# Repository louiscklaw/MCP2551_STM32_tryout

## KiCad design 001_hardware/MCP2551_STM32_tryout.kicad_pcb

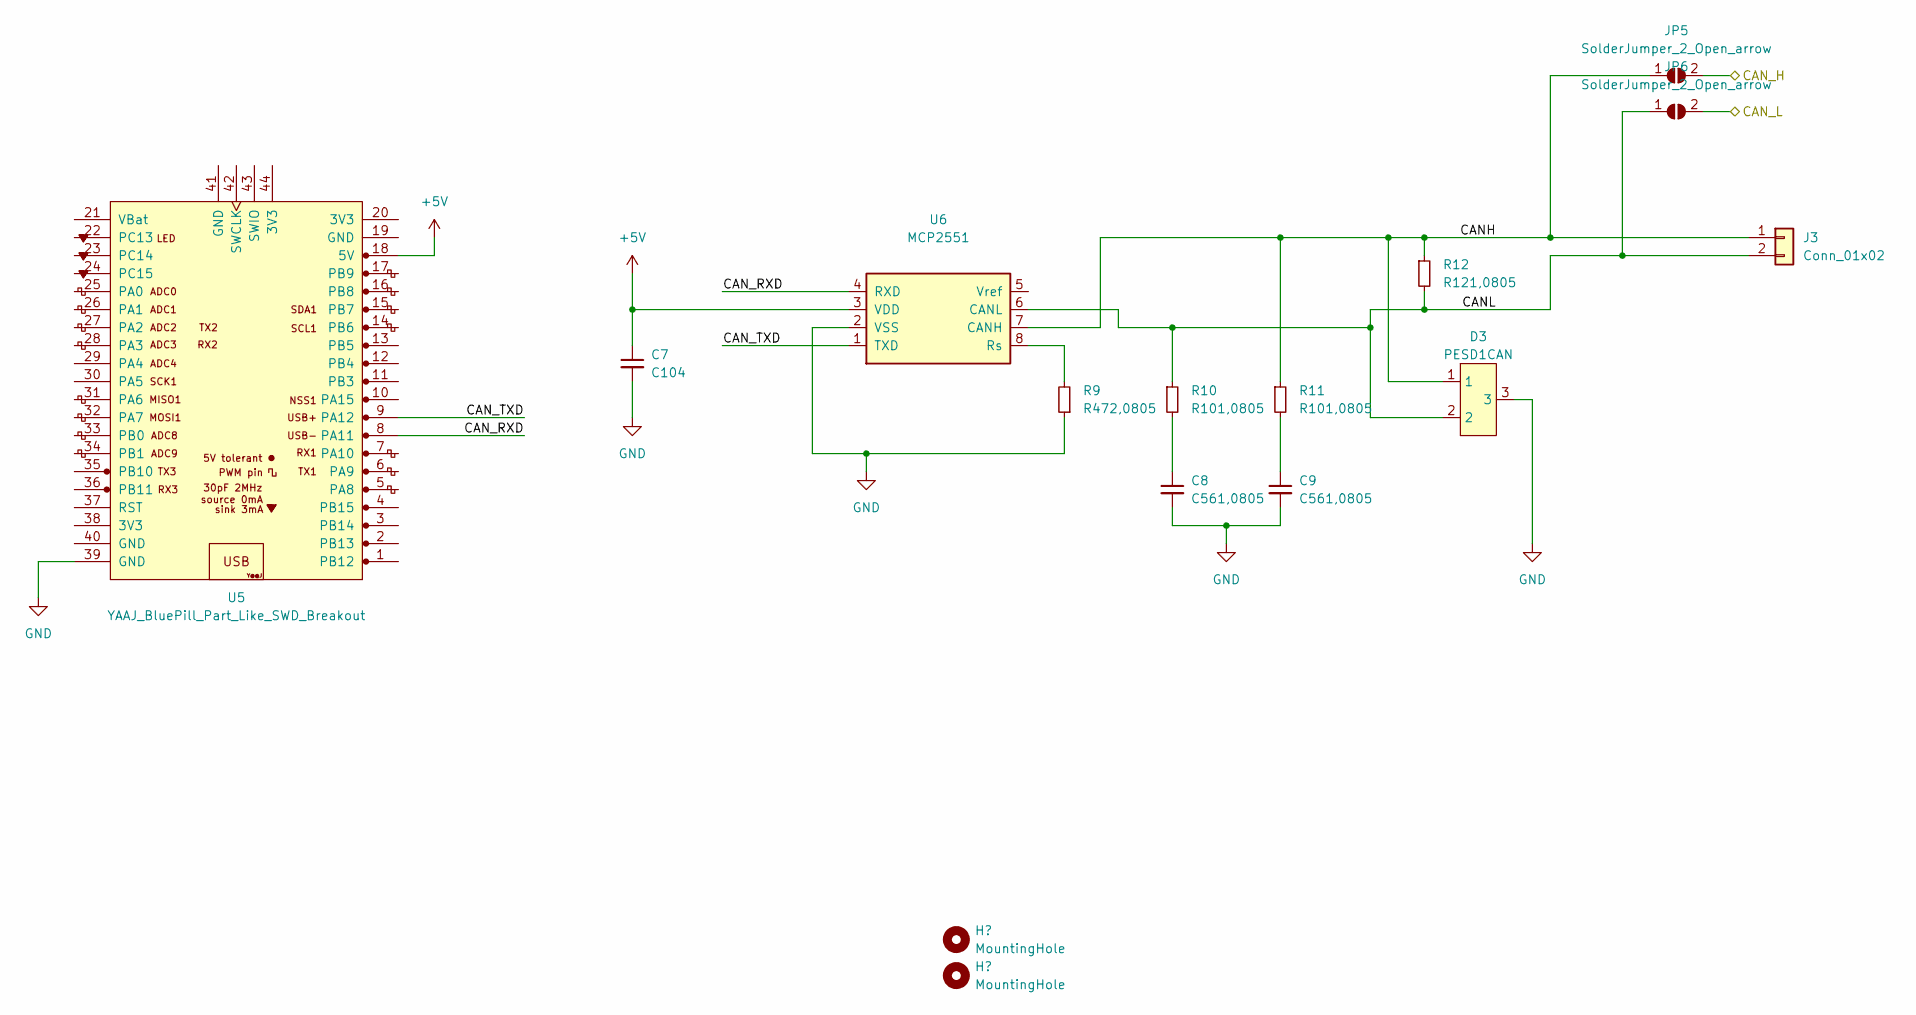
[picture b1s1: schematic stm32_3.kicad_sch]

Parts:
C7: C104; C_0805_2012Metric
C8, C9: C561,0805; C_0805_2012Metric
D3: PESD1CAN; SOT-23
J3: Conn_01x02; PinSocket_1x02_P2.54mm_Vertical
JP5, JP6: SolderJumper_2_Open_arrow; SolderJumper-2_P1.3mm_Open_TrianglePad1.0x1.5mm
R9: R472,0805; R_0805_2012Metric
R10, R11: R101,0805; R_0805_2012Metric
R12: R121,0805; R_0805_2012Metric
U5: YAAJ_BluePill_Part_Like_SWD_Breakout; YAAJ_BluePill_SWD_2
U6: MCP2551; SOIC-8_3.9x4.9mm_P1.27mm

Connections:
+5V: C7.1, U5.18 (5V), U6.3 (VDD); also elsewhere on the board
/stm32_1/CAN_H: JP5.2 (B); also elsewhere on the board
/stm32_1/CAN_L: JP6.2 (B); also elsewhere on the board
/stm32_3/CANH: D3.1, J3.1, JP5.1 (A), R11.1, R12.1, U6.7 (CANH)
/stm32_3/CANL: D3.2, J3.2, JP6.1 (A), R10.1, R12.2, U6.6 (CANL)
/stm32_3/CAN_RXD: U5.8 (PA11), U6.4 (RXD)
/stm32_3/CAN_TXD: U5.9 (PA12), U6.1 (TXD)
GND: C7.2, C8.2, C9.2, D3.3, R9.1, U5.39 (GND), U6.2 (VSS); also elsewhere on the board
unnamed: C8.1, R10.2
unnamed: C9.1, R11.2
unnamed: R9.2, U6.8 (Rs)

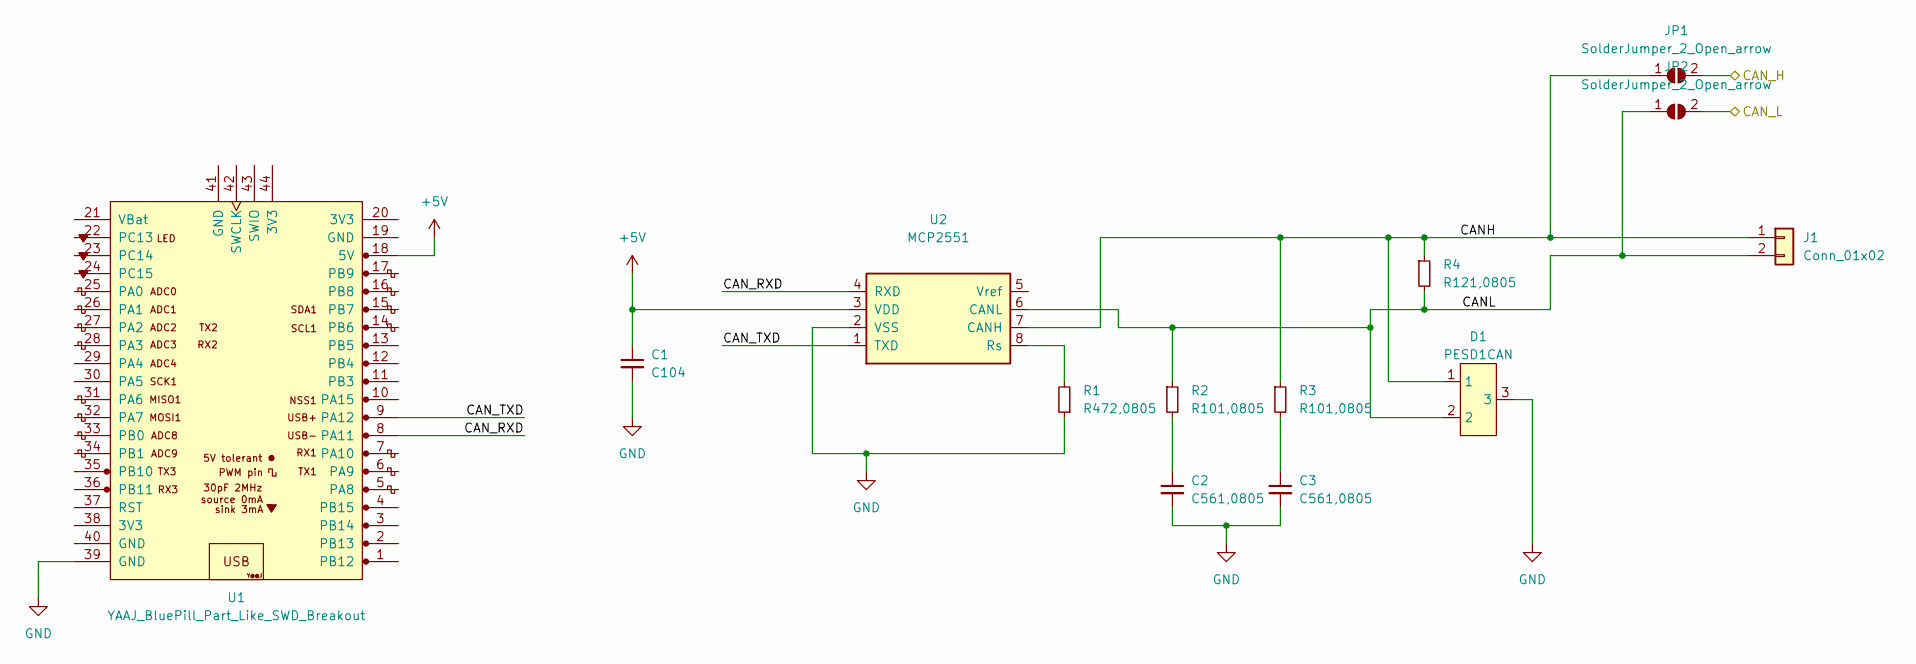
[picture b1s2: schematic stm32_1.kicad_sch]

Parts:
C1: C104; C_0805_2012Metric
C2, C3: C561,0805; C_0805_2012Metric
D1: PESD1CAN; SOT-23
J1: Conn_01x02; PinSocket_1x02_P2.54mm_Vertical
JP1, JP2: SolderJumper_2_Open_arrow; SolderJumper-2_P1.3mm_Open_TrianglePad1.0x1.5mm
R1: R472,0805; R_0805_2012Metric
R2, R3: R101,0805; R_0805_2012Metric
R4: R121,0805; R_0805_2012Metric
U1: YAAJ_BluePill_Part_Like_SWD_Breakout; YAAJ_BluePill_SWD_2
U2: MCP2551; SOIC-8_3.9x4.9mm_P1.27mm

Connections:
+5V: C1.1, U1.18 (5V), U2.3 (VDD); also elsewhere on the board
/stm32_1/CANH: D1.1, J1.1, JP1.1 (A), R3.1, R4.1, U2.7 (CANH)
/stm32_1/CANL: D1.2, J1.2, JP2.1 (A), R2.1, R4.2, U2.6 (CANL)
/stm32_1/CAN_H: JP1.2 (B); also elsewhere on the board
/stm32_1/CAN_L: JP2.2 (B); also elsewhere on the board
/stm32_1/CAN_RXD: U1.8 (PA11), U2.4 (RXD)
/stm32_1/CAN_TXD: U1.9 (PA12), U2.1 (TXD)
GND: C1.2, C2.2, C3.2, D1.3, R1.1, U1.39 (GND), U2.2 (VSS); also elsewhere on the board
unnamed: C2.1, R2.2
unnamed: C3.1, R3.2
unnamed: R1.2, U2.8 (Rs)

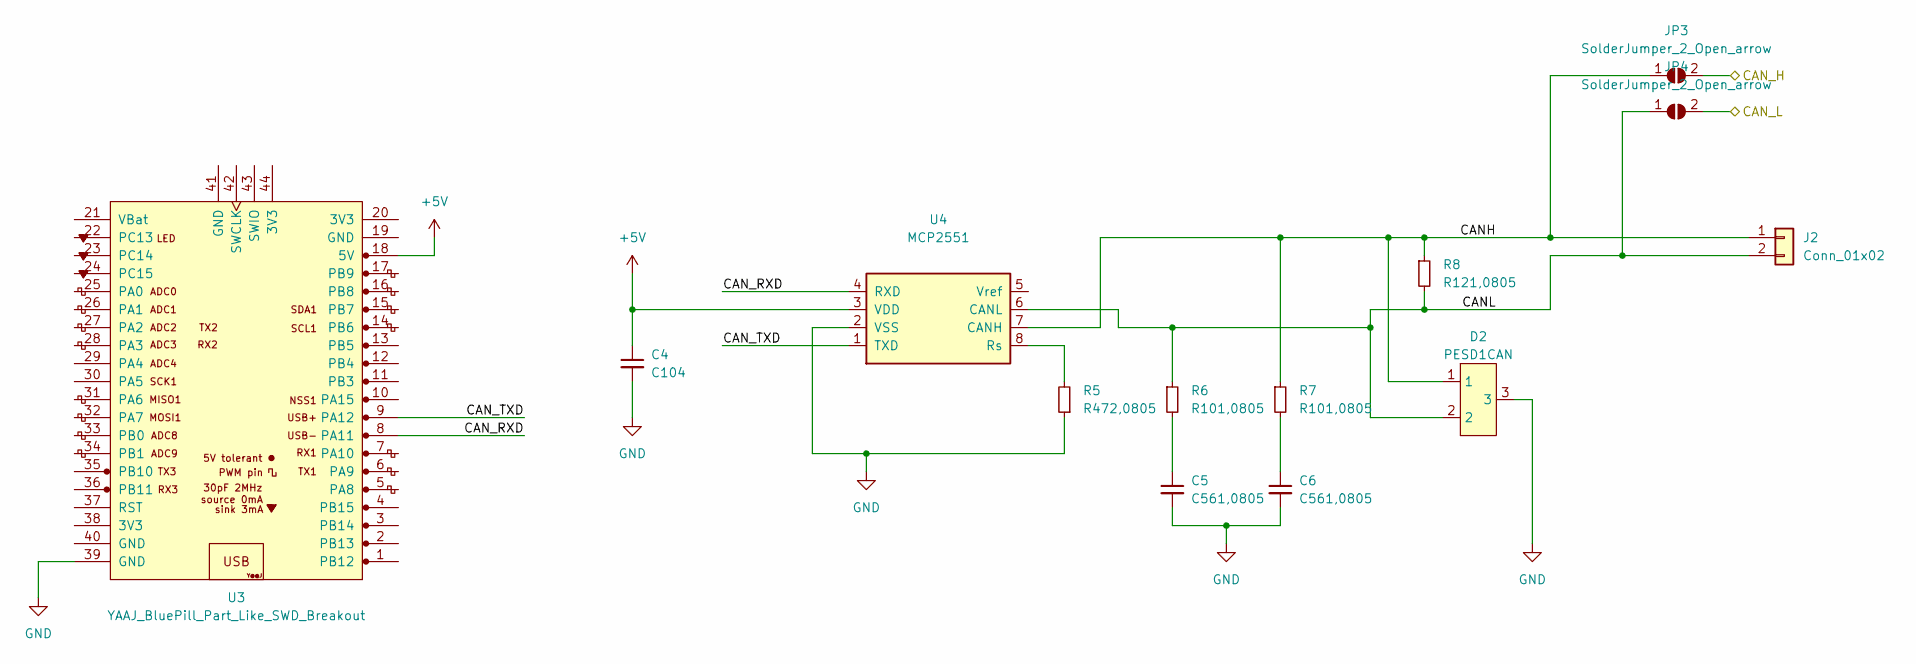
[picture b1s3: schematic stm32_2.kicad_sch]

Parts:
C4: C104; C_0805_2012Metric
C5, C6: C561,0805; C_0805_2012Metric
D2: PESD1CAN; SOT-23
J2: Conn_01x02; PinSocket_1x02_P2.54mm_Vertical
JP3, JP4: SolderJumper_2_Open_arrow; SolderJumper-2_P1.3mm_Open_TrianglePad1.0x1.5mm
R5: R472,0805; R_0805_2012Metric
R6, R7: R101,0805; R_0805_2012Metric
R8: R121,0805; R_0805_2012Metric
U3: YAAJ_BluePill_Part_Like_SWD_Breakout; YAAJ_BluePill_SWD_2
U4: MCP2551; SOIC-8_3.9x4.9mm_P1.27mm

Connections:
+5V: C4.1, U3.18 (5V), U4.3 (VDD); also elsewhere on the board
/stm32_1/CAN_H: JP3.2 (B); also elsewhere on the board
/stm32_1/CAN_L: JP4.2 (B); also elsewhere on the board
/stm32_2/CANH: D2.1, J2.1, JP3.1 (A), R7.1, R8.1, U4.7 (CANH)
/stm32_2/CANL: D2.2, J2.2, JP4.1 (A), R6.1, R8.2, U4.6 (CANL)
/stm32_2/CAN_RXD: U3.8 (PA11), U4.4 (RXD)
/stm32_2/CAN_TXD: U3.9 (PA12), U4.1 (TXD)
GND: C4.2, C5.2, C6.2, D2.3, R5.1, U3.39 (GND), U4.2 (VSS); also elsewhere on the board
unnamed: C5.1, R6.2
unnamed: C6.1, R7.2
unnamed: R5.2, U4.8 (Rs)

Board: 2 copper layers, 43 parts (0 on the bottom side), 25 nets, no tracks yet.

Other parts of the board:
H1, H2, H3, H4: MountingHole; MountingHole_3.1mm_M3,rpi_like

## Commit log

2022-02-12 update,
